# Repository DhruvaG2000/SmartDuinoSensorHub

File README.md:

# SmartDuino

## Introduction

This is an Open Source Project that aims to provide a Smart Sensor Hub with an extremely intuitive user interface using gestures and OLED Display.
It flaunts amazing features like:
- OLED Module for high contrast and low power consumption Display Interface.
- Air Gestures to control music playback and volume (No more BUTTONS!)
- Air Humidity and Temperature Sensing.
- Fun Games using motion detection.
- BLE for low power wireless connectivity with your smartphone.

## Previews

**KiCAD Preview** <br>

**Schematic** <br>

### About: Arduino Nano 33 BLE Sense

The pin diagram is

Features:

1. **Vin:** This pin can be used to power the board with a DC voltage source. If the power is fed through this pin, the USB power source is disconnected. This pin is an INPUT. Respect the voltage limits to assure the proper functionality of the board

2. **5V:** This pin outputs 5V from the board when powered from the USB connector or from the VIN pin of the board.

_Note:_ for it to work, you need to short the VBUS jumper on the back of the board.

3. **3.3V:** This pin outputs 3.3V through the on-board voltage regulator. _Note:_ for ultra low-power functionality, you should cut the 3V3 jumper on the back of the board, and use an external battery at 3V3.
LED ON: This LED is connected to the 5V input from either USB or VIN.

## Hardware Requirements

1. Arduino nano 33 ble sense
2. SH1106_128X64 OLED Display Module (I2C)
3. LED Bar
4. MQ-135 or any other MQ-Series sensor

## Project Milestones

- [X] Provide Air gestures for control
- [ ] IMU for mode toggle:
	- [X] Gyroscope selection of different modes (Left flick and right flick)
	- [ ] Use Accel. for more selections (move up/ down)
- [X] Interface OLED Module with MCU
- [X] Interface MQ-Series Air quality Sensor with MCU
- [ ] Broadcast data over BLE

## PCB Design

## Precautions

1. Use a good quality micro USB type B cable to power the Arduino NANO BLE. Otherwise you may face glitchy OLED text or arduino hangs.
2. Double check the I2C, GPIO and other pins before soldering.

## References:

1. [simple audio player](https://www.arduino.cc/en/Tutorial/SimpleAudioPlayer)
2. [DS-15580-Arduino_Nano_33_BLE_Sense.pdf](https://cdn.sparkfun.com/assets/0/d/8/4/9/DS-15580-Arduino_Nano_33_BLE_Sense.pdf)
3. [arduino-nano-33-ble](https://store.arduino.cc/products/arduino-nano-33-ble)
4. [Datasheet](https://docs.arduino.cc/static/302aa1d360c877c9bbab39f14e2f3ea6/ABX00031-datasheet.pdf)
5. [Useful libraries for accessing on-board sensors](https://www.arduino.cc/en/Guide/NANO33BLESense)

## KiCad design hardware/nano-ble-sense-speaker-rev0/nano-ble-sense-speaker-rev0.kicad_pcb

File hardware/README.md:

# PCB Design for SmartDuino

## Dimensions:

The estimated dimensions for the PCB will be:
- Length = 74.1mm
- Width = 49.6mm
- Height = 36.2mm atleast

The MQ Sensors Module dimensions are:
- L = 32.2mm
- B = 20mm approx.
- H = 15.4mm

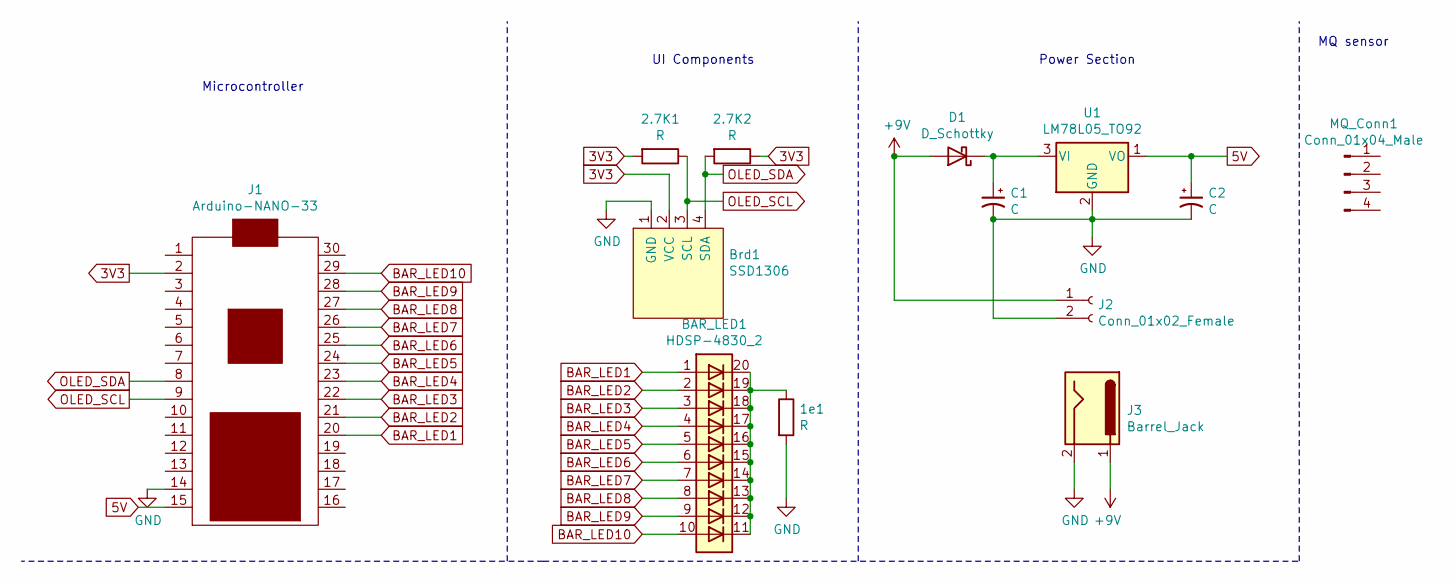
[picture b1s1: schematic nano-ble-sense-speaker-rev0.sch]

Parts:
1e1, 2.7K1, 2.7K2: R; R_Axial_DIN0207_L6.3mm_D2.5mm_P10.16mm_Horizontal
BAR_LED1: HDSP-4830_2; HDSP-4830
Brd1: SSD1306; 128x64OLED
C1, C2: C; CP_Radial_D6.3mm_P2.50mm
D1: D_Schottky; D_SOD-123
J1: Arduino-NANO-33; NANO_33_Socket_Castell
J2: Conn_01x02_Female; PinSocket_1x02_P2.54mm_Vertical
J3: Barrel_Jack; BarrelJack_Horizontal
MQ_Conn1: Conn_01x04_Male; MQ-3
U1: LM78L05_TO92; TO-220-3_Vertical

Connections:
3V3: 2.7K1.2, 2.7K2.1, Brd1.2 (VCC), J1.2
5V: C2.1, J1.15, U1.1 (VO)
+9V: D1.2 (A), J2.1, J3.1
BAR_LED1: BAR_LED1.1 (A), J1.20
BAR_LED2: BAR_LED1.2 (A), J1.21
BAR_LED3: BAR_LED1.3 (A), J1.22
BAR_LED4: BAR_LED1.4 (A), J1.23
BAR_LED5: BAR_LED1.5 (A), J1.24
BAR_LED6: BAR_LED1.6 (A), J1.25
BAR_LED7: BAR_LED1.7 (A), J1.26
BAR_LED8: BAR_LED1.8 (A), J1.27
BAR_LED9: BAR_LED1.9 (A), J1.28
BAR_LED10: BAR_LED1.10 (A), J1.29
GND: 1e1.2, Brd1.1 (GND), C1.2, C2.2, J1.14, J2.2, J3.2, U1.2 (GND)
unnamed: 1e1.1, BAR_LED1.11 (K), BAR_LED1.12 (K), BAR_LED1.13 (K), BAR_LED1.14 (K), BAR_LED1.15 (K), BAR_LED1.16 (K), BAR_LED1.17 (K), BAR_LED1.18 (K), BAR_LED1.19 (K), BAR_LED1.20 (K)
unnamed: C1.1, D1.1 (K), U1.3 (VI)
OLED_SCL: 2.7K1.1, Brd1.3 (SCL), J1.9
OLED_SDA: 2.7K2.2, Brd1.4 (SDA), J1.8

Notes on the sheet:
Microcontroller
UI Components
Power Section
MQ sensor

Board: 2 copper layers, 13 parts (0 on the bottom side), 18 nets, no tracks yet.

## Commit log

2021-09-14 Start writing project initial report
2021-09-14 create kicad project
2021-09-22 Create OLED_Basic_Controls.ino
    Working:
    - Volume level up and down
    - music next and previous
2021-09-22 Create HTS221_OLED_test.ino
    - basic temperature and humidity display
2021-09-22 add datasheet
2021-09-27 Add previews to README
    This is the first ever preview of a non-functional design plan for this
    project
2021-09-27 remove top image
2021-09-27 add features
2021-09-27 firmware: Add platform IO Folder
    This code is a singular collection of all the OLED + Sensor basic tests
    that you can run as required
2021-09-27 Update list of files to ignore
2021-09-27 Start writing actual firmware for this project
2021-09-27 add a temp. offset
2021-09-28 platformio-test: improved code formatting
2021-09-28 pfio-test: Improve humidity and temp algo
    Now take average of 5 readings and then display them on the OLED to get
    better accuracy.
    Also added offset values to tweak and adjust the values
2021-09-28 create a basic example using mbed rtos
    This example just reads the gyro and accel reading in parallel using
    mdeb rtos threads
2021-09-28 Revert "pfio-test: Improve humidity and temp algo"
    This reverts commit 7467a0f09d4e94d024670cf9a998470cccf9fb46.
    This addition is giving very random results and out of range humidity
    values. Will need to see why the sensor is not performing properly
2021-09-28 pfio-test: dht: add offsets
    Add offset variables at the beginning to help calibrate the temp and
    humidity sensor readings
2021-09-29 FW: Create 3 RT Threads
    This makes sure that accel and gyro reading are taken continuously and
    also the choice maker function runs in parallel such that after any
    change of state/choice the required loopXX() is called.
2021-09-29 rename pt 1: firmware:sensorSetup.cpp and sensorSetup.h
2021-09-29 rename and refactor: firmware: sensorManager
    sensorManager now has 2 classes one for setup member other for loop.
    The code has been highly refactored and following features were added:
    - Intuitive names to functions like ``setupIMU()`` instead of part names
    - Now we have a placeholder function with ``switch`` that will help with
    selection of program to run.
2021-09-29 modified: README.md
2021-09-29 Setup workflow to build fw
2021-09-29 rename few workflow names
2021-09-29 test commit
2021-09-29 Tested basic tone example
    Also added a example of some song player, but yet to test it
2021-10-04 Make Debugging Cleaner
    Added macro to define all Serial.print statements to make debugging the
    code easy and clean. Just define DEBUG 1 for getting serial logs, and
    un-define it to get none.
2021-10-13 add pitches file which will be used later for audio program
2021-10-14 Board is probably incapable of parallel processing
    hence reconsidering rtos approach.
    Might use interrupts or some other smarter methodsthat do not
    necessarily require parallel processing.
2021-10-14 Restart writing firmware
    Scrapped the RTOS part and this time added the actual implementations of
    all relevant functions under sensorManager.cpp
    NOTE: The OLED is a bit loose so debugging programs might seem like
    there is a source code issue but it might be a hardware issue so double
    check program at this particular commit, and if everything works then it
    may be a software issue otherwise if even at this stage the OLED does
2021-10-14 Combine Accel + Mode Sel
    Finally! The accelerometer changes triggers a change in the mode. This
    code has been tested thoroughly and works fine.
    Next goal: play a music/tone file
2021-10-14 refactoring and add LED blink at mode change
    - refactor missed out Serial statements into debuglog()
    - Add LED blink everytime the board s turned up or down to indicate changed mode.
    Bugs to keep track:
    The switch after humidity temp mode sort of feels like it hangs, but it
    is because the previous screen left was of hum/temp. This can be easily
    fixed by setting the detecting gestures.. screen everytime we change
2021-10-14 Add dco check to workflows
2021-10-17 Update preview image
2021-10-17 Make first PCB design
    PCB Design in KiCAD now has:
    - OLED 1.3inch
    - power supply using LM7805 and capacitors
    TODO:
    - Add I2S module either as the breakout board of on the PCB as an SMD
    comp.
2021-10-17 Add pull up resistors to I2C
2021-12-12 Minor VSCode settings change
2021-12-12 firmware: Read and Display MQ Sensor RAW
    Code has been tested and it works with a MQ-135 sensor connected to:
    SENSOR | Arduino
    - Analog --> A0
    - Vcc --> 3.3V
    - GND --> GND
    - Digital --> N/A
2021-12-12 Updated Project outcomes and TODOs
2021-12-27 Rearrange hardware directory structure
2021-12-27 Added bar LED and a type C library
    The plan is to later use a type C port to power the circuit.
    Currently there is also a library that got updated in kicad but not in our project hence it will also need updating.
2021-12-27 Update README: Add dimensions
2021-12-27 Media: Add updated sch photos
2021-12-27 Minor fix in naming
2021-12-27 Update PCB design
    - Now includes bar LED with all it's connections
    - 3D files for OLED and arduino
    TODO:
    - Draw traces
    - Make drill holes for mounting the OLED steadily
    - Probably add a Li ion charging circuit
2021-12-27 Add Libraries
2021-12-28 Add MQ Sensor dims
2021-12-28 Add height of MQ sensor
2021-12-28 Created MQ 3 footprint and assigned 3D
2022-01-02 update pin diag
2022-01-02 Minor changes
2022-01-02 Move serial begin to main.cpp
2022-01-02 Create VAR_LED example
    Example has been tested and it works OK.. There seems to be bad soldering other than that it is fine
2022-01-04 Add pressure sensor library
    also increase the monitor baud rate
2022-01-04 Add pressure sensor
2022-01-04 minor fix
2022-01-05 add pressure sensor libs to workflow
